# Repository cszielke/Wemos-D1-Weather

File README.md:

# Wemos-D1-Weather
Weatherstation with Wemos-D1-Mini and RFM69 Receiver

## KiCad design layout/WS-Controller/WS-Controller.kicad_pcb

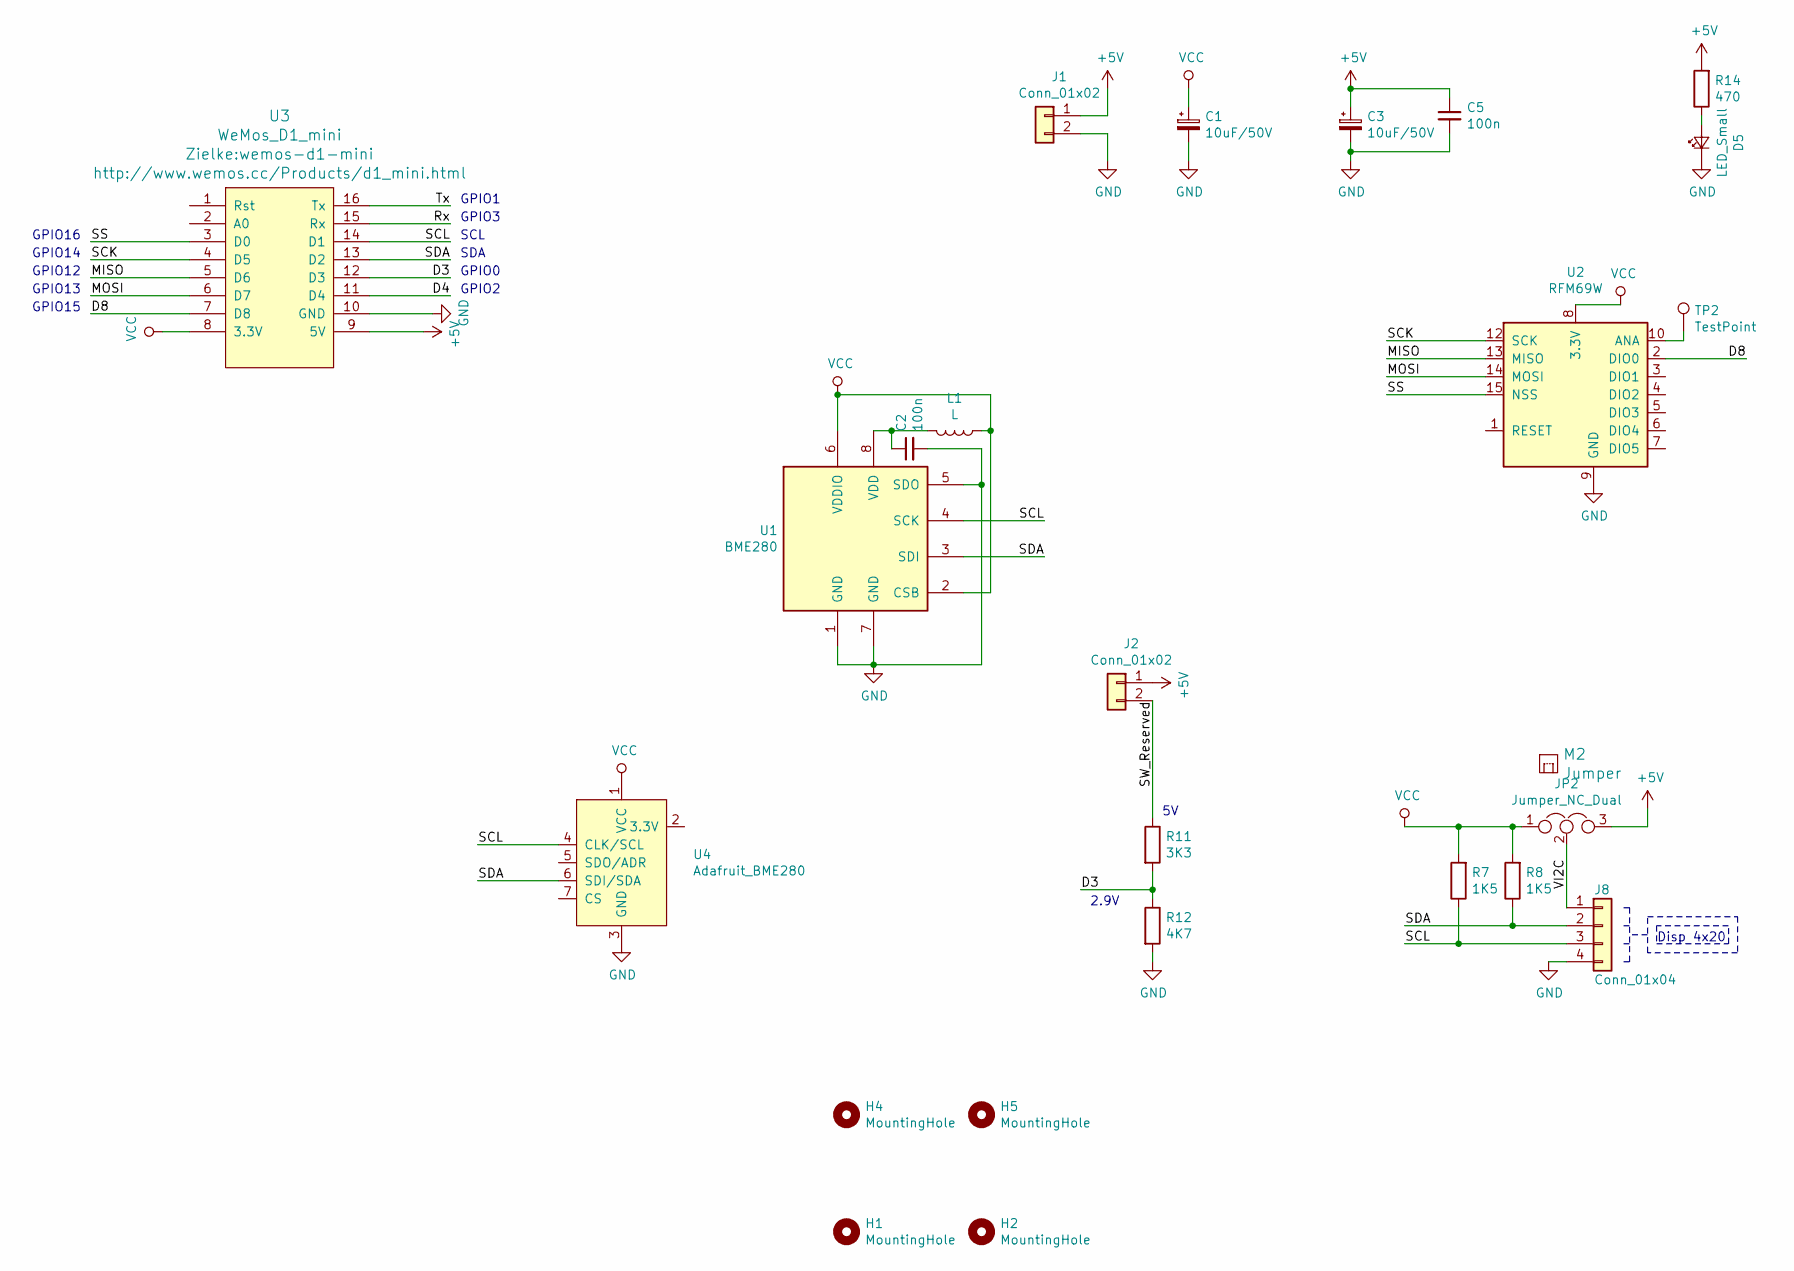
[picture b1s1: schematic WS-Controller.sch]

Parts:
C1, C3: 10uF/50V; CP_Radial_D6.3mm_P2.50mm
C2, C5: 100n; C_0603_1608Metric
D5: LED_Small; LED_D3.0mm
H1, H2, H4, H5: MountingHole; MountingHole_4.3mm_M4_ISO14580
J1, J2: Conn_01x02; TerminalBlock_Phoenix_MKDS-1,5-2-5.08_1x02_P5.08mm_Horizont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
J8: Conn_01x04; Molex_KK-254_AE-6410-04A_1x04_P2.54mm_Vertical
JP2: Jumper_NC_Dual; PinHeader_1x03_P2.54mm_Vertical
L1: L; L_2010_5025Metric
M2: Jumper
R7, R8: 1K5; R_0603_1608Metric
R11: 3K3; R_0603_1608Metric
R12: 4K7; R_0603_1608Metric
R14: 470; R_0603_1608Metric
TP2: TestPoint; TestPoint_THTPad_2.0x2.0mm_Drill1.0mm
U1: BME280; Bosch_LGA-8_2.5x2.5mm_P0.65mm_ClockwisePinNumbering
U2: RFM69W; HOPERF_RFM69HW
U3: WeMos_D1_mini; wemos-d1-mini
U4: Adafruit_BME280; ADAFRUIT_BME280

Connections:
+5V: C3.1, C5.1, J1.1, J2.1, JP2.3, R14.2, U3.9 (5V)
/D3: R11.2, R12.1, U3.12 (D3)
/D4: U3.11 (D4)
/D8: U2.2 (DIO0), U3.7 (D8)
/MISO: U2.13 (MISO), U3.5 (D6)
/MOSI: U2.14 (MOSI), U3.6 (D7)
/Rx: U3.15 (Rx)
/SCK: U2.12 (SCK), U3.4 (D5)
/SCL: J8.3, R7.1, U1.4 (SCK), U3.14 (D1), U4.4 (CLK/SCL)
/SDA: J8.2, R8.1, U1.3 (SDI), U3.13 (D2), U4.6 (SDI/SDA)
/SS: U2.15 (NSS), U3.3 (D0)
/SW_Reserved: J2.2, R11.1
/Tx: U3.16 (Tx)
/VI2C: J8.1, JP2.2
GND: C1.2, C2.2, C3.2, C5.2, D5.1 (K), J1.2, J8.4, R12.2, U1.1 (GND), U1.5 (SDO), U1.7 (GND), U2.9 (GND), U2.11 (GND), U3.10 (GND), U4.3 (GND)
unnamed: C2.1, L1.2, U1.8 (VDD)
unnamed: D5.2 (A), R14.1
unnamed: TP2.1, U2.10 (ANA)
VCC: C1.1, JP2.1, L1.1, R7.2, R8.2, U1.2 (CSB), U1.6 (VDDIO), U2.8 (3.3V), U3.8 (3.3V), U4.1 (VCC)

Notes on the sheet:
2.9V
Disp 4x20
GPIO1
GPIO3
SCL
SDA
GPIO0
GPIO2
GPIO16
GPIO14
GPIO12
GPIO13
GPIO15

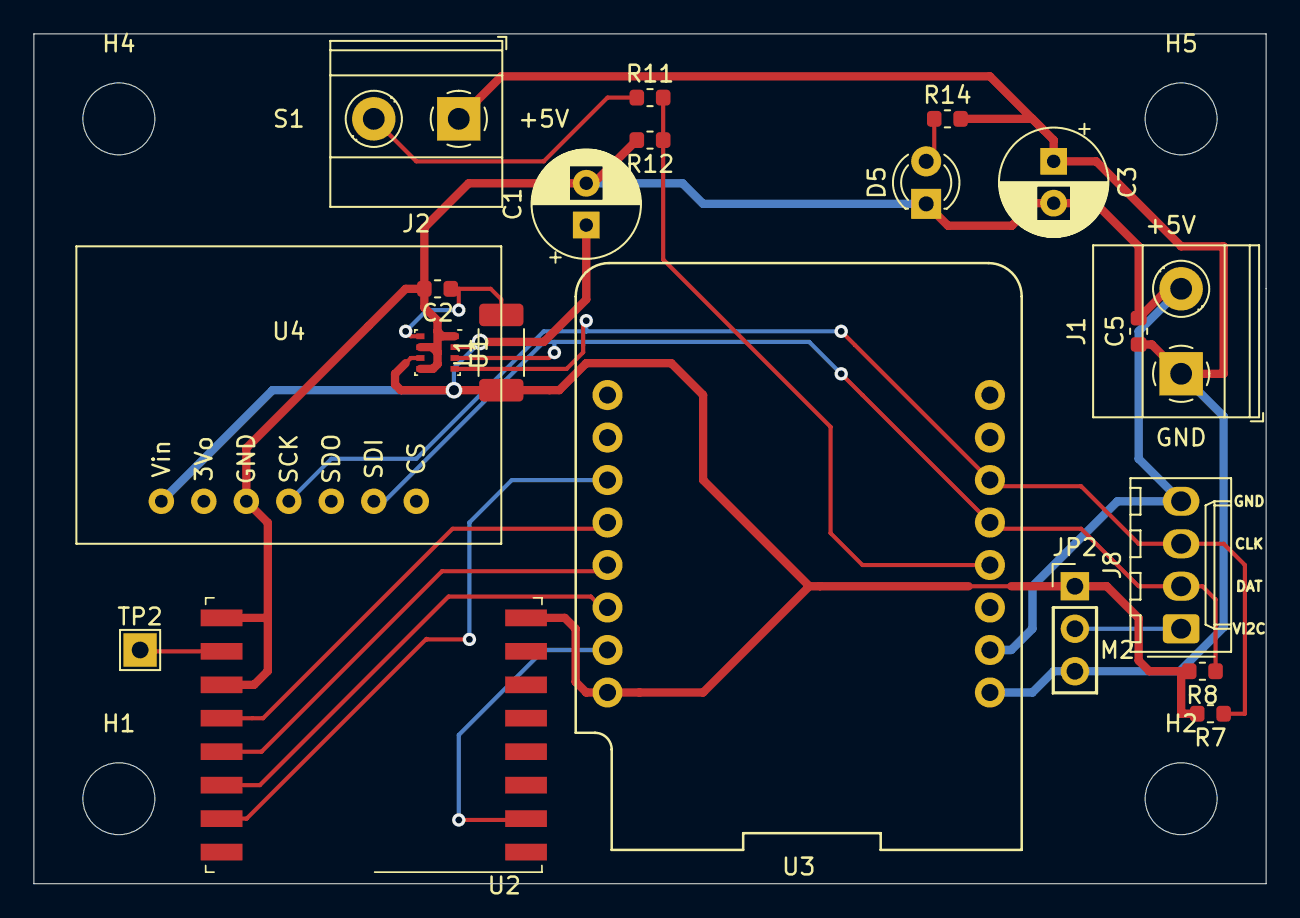
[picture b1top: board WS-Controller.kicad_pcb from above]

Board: 2 copper layers, 73.7 x 50.8 mm, 25 parts (0 on the bottom side), 16 nets.

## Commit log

2021-05-14 Initial checkin
2021-05-14 Parameter angepasst
2021-05-14 Publisch von gefakten Values
2021-05-15 Auslesen BME280 implementiert
2021-05-16 AVG der Batteriespannung, 1s looptime
2021-05-16 Bug: Keine Messung ohne takeForcedMess.
2021-06-17 RFM69 lib implementiert
2021-06-17 Readme und gitignore angepasst
2021-06-17 Docs Verzeichnis ins root
2021-06-17 Theme auf readthedocs gesetzt
2021-06-17 remove - pymdownx.extra
2021-06-17 pymdownx Extention komplett entfernt
2021-06-17 requirements.txt
2021-06-17 Badge für ReadTheDocs
2021-06-17 typo
2021-06-17 About
2021-06-17 mkdocs extentions in requirements.txt
2021-06-17 conf mkdocs
2021-06-17 Tabelle korrigiert
2021-06-17 mkdocs.yaml für localen build angepasst
2021-06-19 Klasse für RFM69
2021-06-19 Schaltplan für Wemos-D1
2021-06-22 Verdrahtung entfernt
2021-06-22 RFMOOK Lib entfernt und eigene hinzugefügt
2021-07-28 Set Frequency
2021-09-01 External Wind and Rain Sensor
